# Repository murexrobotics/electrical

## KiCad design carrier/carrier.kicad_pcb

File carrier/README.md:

# Documentation

<https://docs.murexrobotics.com/elec/boards/carrier>

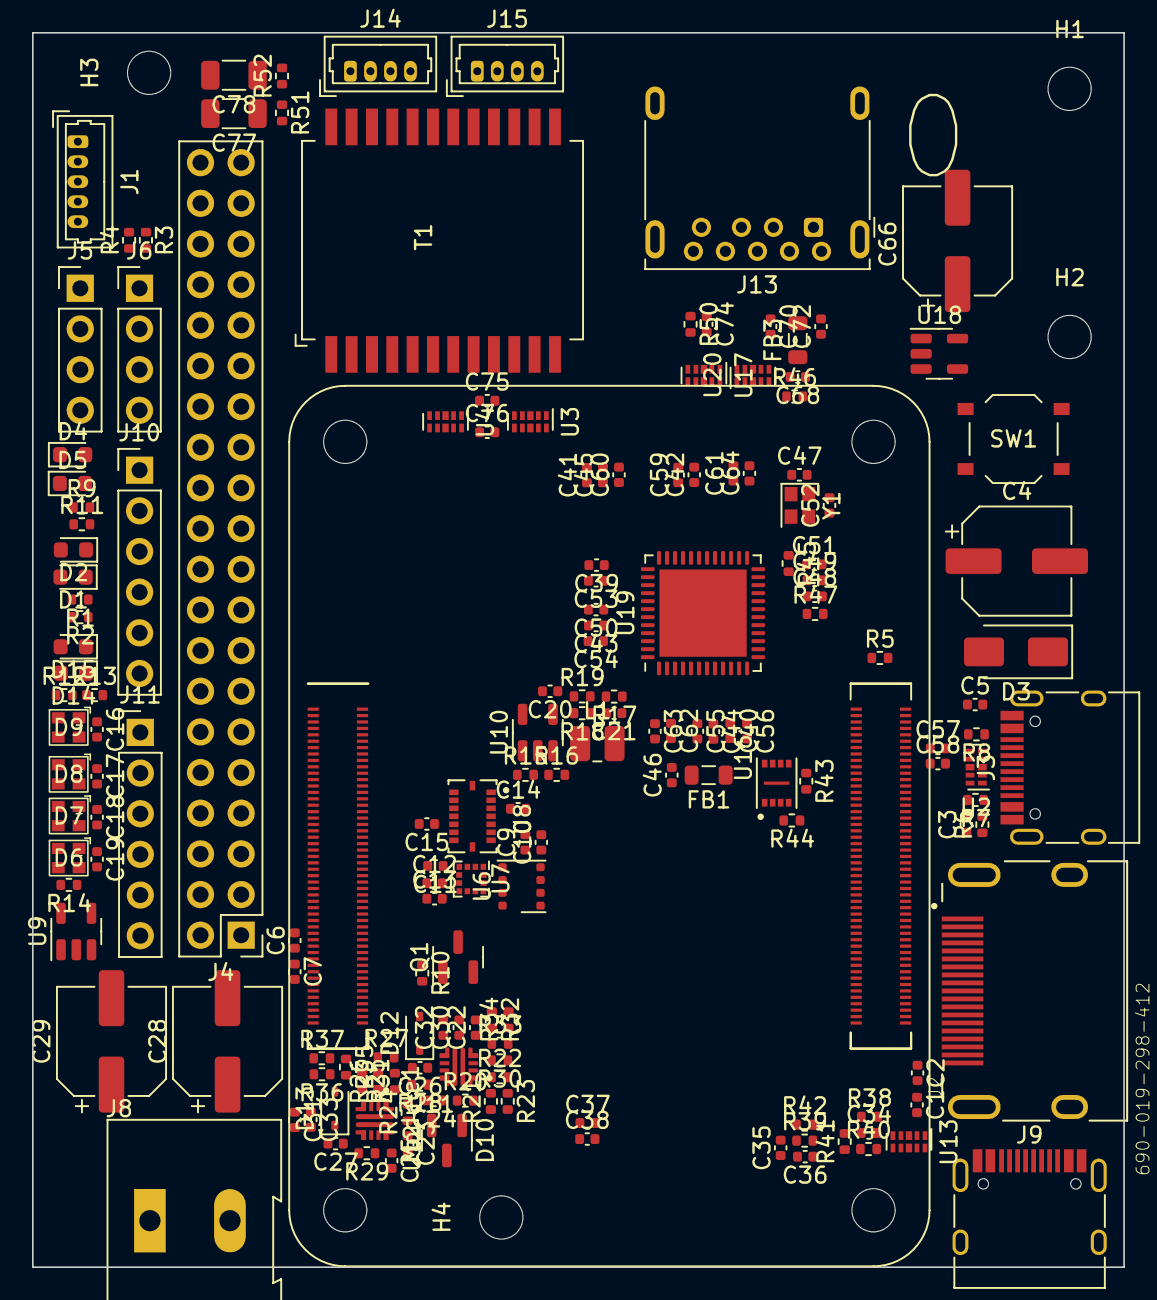
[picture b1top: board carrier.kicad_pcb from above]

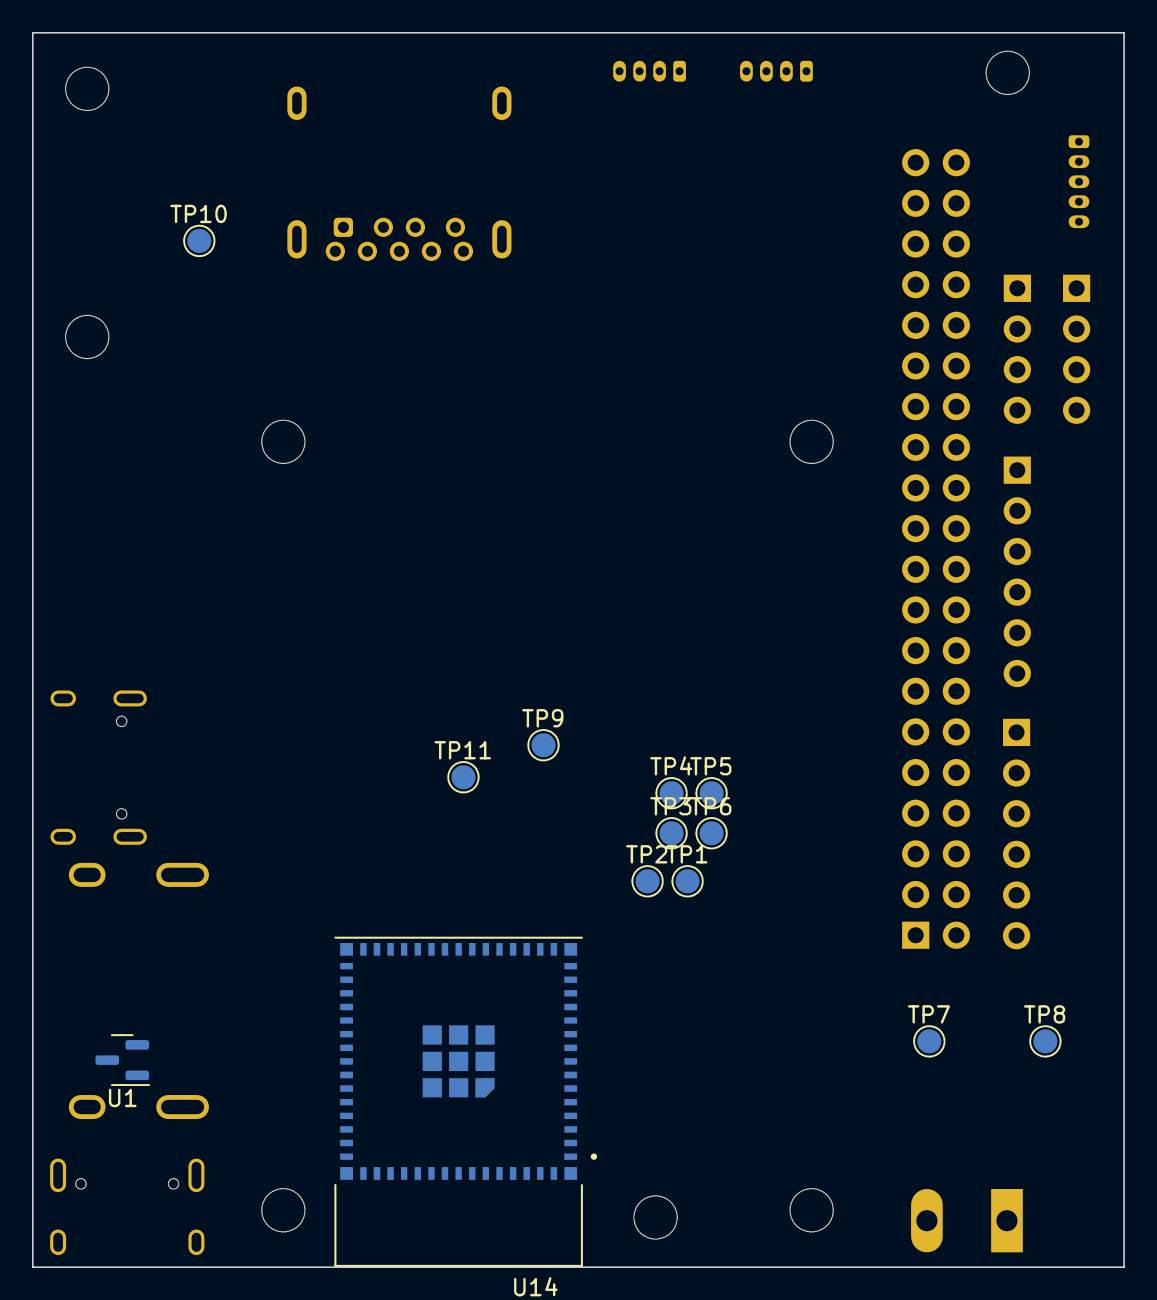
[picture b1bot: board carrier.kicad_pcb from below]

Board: 4 copper layers, 68.2 x 77.1 mm, 192 parts (13 on the bottom side), 178 nets, no tracks yet.

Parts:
C1, C2, C3, C5, C6, C9, C10, C11, C13, C14, C15, C34, C39, C40, C41, C42, C57, C58, C61, C62, C70, C72, C74: 100nF; C_0402_1005Metric
C4, C28, C29, C66: 150uF; CP_Elec_6.3x7.7
C7, C20, C30, C31, C32, C33, C46, C68: 10uF; C_0402_1005Metric
C12, C36: 1uF; C_0402_1005Metric
C16, C17, C18, C19, C35, C38, C75, C76: 0.1uF; C_0402_1005Metric
C21, C47, C52: 22pF; C_0402_1005Metric
C22, C23: 1uF X5R; C_0402_1005Metric
C24, C25: 2.2nF; C_0402_1005Metric
C26, C27: 3.3nF; C_0402_1005Metric
C37: 22uF; C_0402_1005Metric
C43, C44, C45, C48, C49, C50, C51, C53, C54, C55, C56, C59, C60, C63, C64: 10nF; C_0402_1005Metric
C77, C78: 1nF 2KV (1206); C_1206_3216Metric
D1: 5V; LED_0603_1608Metric
D2: 3.3V; LED_0603_1608Metric
D3: SS54; D_SMA
D4, D14: LED Green; LED_0603_1608Metric
D5: LED RED; LED_0603_1608Metric
D6, D7, D8, D9: NEOPIXEL; SK6812-EC20
D10: PSM712; SOT-23
D12, D13: 1N5819WS; D_SOD-323
D15: LED Orange; LED_0603_1608Metric
FB1, FB3: BLM21PG600SN1; L_0805_2012Metric
H1, H2, H3, H4: MountingHole; MountingHole_2.7mm_M2.5
H5: CM4 GPIO Hirose 2x50; Raspberry-Pi-4-Compute-Module-No-Outline-No-Pads
H6: CM4 High Speed Hirose 2x50; Raspberry-Pi-4-Compute-Module-No-Outline-No-Pads
J1: UART; Molex_PicoBlade_53047-0510_1x05_P1.25mm_Vertical
J2: 690-019-298-412; EDAC 690-019-298-412
J3, J9: USB_C_Receptacle_USB2.0; USB_C_Receptacle_HRO_TYPE-C-31-M-12
J4: THD-20-R; PinHeader_2x20_P2.54mm_Vertical
J5, J6: I2C; PinHeader_1x04_P2.54mm_Vertical
J8: External 5V Input; TerminalBlock_Altech_AK300-2_P5.00mm
J10: ESP GPIO 1; PinHeader_1x06_P2.54mm_Vertical
J11: ESP GPIO 2; PinHeader_1x06_P2.54mm_Vertical
J13: USB3_A; USB3_A_Molex_48393-001
J14, J15: Conn_01x04; Molex_PicoBlade_53047-0410_1x04_P1.25mm_Vertical
L1: 2.2uH; L_1008_2520Metric
Module1: ComputeModule4; Raspberry-Pi-4-Compute-Module
Q1: SS8550; SOT-23
R1, R2, R5, R10: 2.2k; R_0402_1005Metric
R3, R4, R23, R33, R42, R44, R47: 10k; R_0402_1005Metric
R6, R38, R50: 1M; R_0402_1005Metric
R7, R8: 56k; R_0402_1005Metric
R9, R11, R12, R13: 1k; R_0402_1005Metric
R14: 470; R_0402_1005Metric
R15, R16: 15k; R_0402_1005Metric
R17: 12k; R_0402_1005Metric
R18, R19: 8.2k; R_0402_1005Metric
R20, R24: 470k; R_0402_1005Metric
R21: 30k; R_0402_1005Metric
R22: 120k; R_0402_1005Metric
R25, R30, R31, R32, R35, R43: 47k; R_0402_1005Metric
R26: 220k; R_0402_1005Metric
R27: 33k; R_0402_1005Metric
R28: 760; R_0402_1005Metric
R29: 1.5k; R_0402_1005Metric
R34, R40, R41: 5.1k; R_0402_1005Metric
R36: 27k; R_0402_1005Metric
R37: 1.2k; R_0402_1005Metric
R39: 0; R_0402_1005Metric
R45: 680; R_0402_1005Metric
R46: 1.6k; R_0402_1005Metric
R51, R52: 75; R_0402_1005Metric
SW1: ESP RST; SW_Push_1P1T_XKB_TS-1187A
T1: QT24A23
TP1, TP2, TP3, TP4, TP5, TP6, TP7, TP8, TP9, TP10, TP11: TestPoint_Pad_D1.5mm
U1: RT9742SNGV; SOT-23
U2, U3, U4, U13, U17, U20: TPD4EUSB30; USON-10_2.5x1.0mm_P0.5mm
U6: BME680; Bosch_LGA-8_3x3mm_P0.8mm_ClockwisePinNumbering
U7: LIS3MDL; LGA-12_2x2mm_P0.5mm
U8: BMI088; PQFN50P450X300X100-16N
U9: SN74LV1T34DCK; SOT-23-5
U10: AP3429KTTR-G1; TSOT-23-5
U11, U12: TPS259474ARPWR; TPS259474
U14: ESP32-S3-MINI-1-N8; ESP32-S3-MINI-1
U16: W25X40CLUXIG
U18: AP2191; SOT-23-5
U19: uPD720202; QFN-48-1EP_7x7mm_P0.5mm_EP5.45x5.45mm
Y1: 24MHz; Crystal_SMD_2016-4Pin_2.0x1.6mm

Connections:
+3.3v: C9.1, C10.1, C14.1, C15.1, C29.1, C31.1, C33.1, C37.1, C38.1, C41.1, C43.1, C45.1, C49.1, C51.1, C54.1, C56.1, D4.2 (A), D13.1 (K), D14.2 (A), D15.2 (A), FB1.1, J4.1, J4.17, J5.3, J6.3, Q1.2 (E), R2.1, R3.1, R4.2, R15.1, R30.1, R31.1, R35.1, R42.1, R43.2, R44.1, R47.2, TP8.1, U6.2 (CSB), U6.5 (SDO), U6.6 (VDDIO), U6.8 (VDD), U7.10 (~CS), U8.3 (VDD), U8.11 (VDDIO), U12.6 (OUT), U14.3 (3V3), U16.7 (~HOLD), U16.8 (VCC), U19.12 (VDD33), U19.22 (VDD33), U19.34 (VDD33), U19.43 (VDD33)
/+1.05v: C21.1, C39.1, C40.1, C42.1, C44.1, C48.1, C50.1, C53.1, C55.1, C59.1, C60.1, L1.2, R17.1, TP9.1, U19.6 (VDD10), U19.9 (VDD10), U19.21 (VDD10), U19.30 (VDD10), U19.33 (VDD10), U19.39 (VDD10), U19.42 (VDD10)
/+5v: C1.1, C4.1, C5.1, C6.1, C7.1, C20.1, C28.1, C30.1, C32.1, D3.2 (A), D12.1 (K), J4.2, J4.4, Module1.77 (+5v_(Input)), Module1.79 (+5v_(Input)), Module1.81 (+5v_(Input)), Module1.83 (+5v_(Input)), Module1.85 (+5v_(Input)), Module1.87 (+5v_(Input)), R1.1, R7.2, R8.2, R32.1, TP7.1, U1.1 (IN), U10.4 (VIN), U11.6 (OUT), U18.5 (IN)
/CM4_GPIO/+3.3v_REF: Module1.78 (GPIO_VREF(1.8v/3.3v_Input)), Module1.84 (+3.3v_(Output)), Module1.86 (+3.3v_(Output))
/CM4_GPIO/BT_nDis: J4.27, Module1.89 (WiFi_nDisable), Module1.91 (BT_nDisable)
/CM4_GPIO/CT1: T1.7 (CT1), T1.10 (CT1)
/CM4_GPIO/CT2: C76.1, T1.1 (CT2), T1.4 (CT2)
/CM4_GPIO/ETH_LEDG: Module1.17 (Ethernet_nLED2(3.3v)), R12.2
/CM4_GPIO/ETH_LEDY: Module1.15 (Ethernet_nLED3(3.3v)), R13.2
/CM4_GPIO/GPIO6: J4.31, Module1.30 (GPIO6)
/CM4_GPIO/GPIO12: J4.32, Module1.31 (GPIO12)
/CM4_GPIO/GPIO13: J4.33, Module1.28 (GPIO13)
/CM4_GPIO/GPIO16: J4.36, Module1.29 (GPIO16)
/CM4_GPIO/GPIO17: J4.11, Module1.50 (GPIO17)
/CM4_GPIO/GPIO18: J4.12, Module1.49 (GPIO18), U9.2 (A)
/CM4_GPIO/GPIO19: J4.35, Module1.26 (GPIO19)
/CM4_GPIO/GPIO20: J4.38, Module1.27 (GPIO20)
/CM4_GPIO/GPIO21: J4.40, Module1.25 (GPIO21)
/CM4_GPIO/GPIO22: J4.15, Module1.46 (GPIO22)
/CM4_GPIO/GPIO23: J4.16, Module1.47 (GPIO23)
/CM4_GPIO/GPIO24: J4.18, Module1.45 (GPIO24)
/CM4_GPIO/GPIO25: J4.22, Module1.41 (GPIO25)
/CM4_GPIO/GPIO26: J4.37, Module1.24 (GPIO26)
/CM4_GPIO/GPIO27: J4.13, Module1.48 (GPIO27)
/CM4_GPIO/Neopixel/+5v: C16.2, C17.2, C18.2, C19.2, D6.1 (VDD), D7.1 (VDD), D8.1 (VDD), D9.1 (VDD), U9.5 (VCC)
/CM4_GPIO/REF1: C78.1, R52.2
/CM4_GPIO/REF2: C77.1, R51.2
/CM4_GPIO/TRD0+: J14.1, T1.23 (TX2+)
/CM4_GPIO/TRD0-: J14.2, T1.22 (TX2-)
/CM4_GPIO/TRD0_N: Module1.10 (Ethernet_Pair0_N), T1.3 (TD2-), U4.4 (D2+), U4.7
/CM4_GPIO/TRD0_P: Module1.12 (Ethernet_Pair0_P), T1.2 (TD2+), U4.5 (D2-), U4.6
/CM4_GPIO/TRD1+: J14.3, T1.20 (RX2+)
/CM4_GPIO/TRD1-: J14.4, T1.19 (RX2-)
/CM4_GPIO/TRD1_N: Module1.6 (Ethernet_Pair1_N), T1.6 (RD2-), U4.2 (D1-), U4.9
/CM4_GPIO/TRD1_P: Module1.4 (Ethernet_Pair1_P), T1.5 (RD2+), U4.1 (D1+), U4.10
/CM4_GPIO/TRD2+: J15.1, T1.17 (TX1+)
/CM4_GPIO/TRD2-: J15.2, T1.16 (TX1-)
/CM4_GPIO/TRD2_N: Module1.9 (Ethernet_Pair2_N), T1.9 (TD1-), U3.4 (D2+), U3.7
/CM4_GPIO/TRD2_P: Module1.11 (Ethernet_Pair2_P), T1.8 (TD1+), U3.5 (D2-), U3.6
/CM4_GPIO/TRD3+: J15.3, T1.14 (RX1+)
/CM4_GPIO/TRD3-: J15.4, T1.13 (RX1-)
/CM4_GPIO/TRD3_N: Module1.5 (Ethernet_Pair3_N), T1.12 (RD1-), U3.2 (D1-), U3.9
/CM4_GPIO/TRD3_P: Module1.3 (Ethernet_Pair3_P), T1.11 (RD1+), U3.1 (D1+), U3.10
/CM4_GPIO/nEXTRST: Module1.100 (nEXTRST), U19.11 (PONRSTB)
/CM4_GPIO/nPWR_LED: Module1.95 (nPI_LED_PWR), R10.1
/CM4_GPIO/nRPIBOOT: J4.28, Module1.93 (nRPIBOOT)
/CM4_HighSpeed/HDMI0_CEC: J2.13 (CEC), Module1.151 (HDMI0_CEC)
/CM4_HighSpeed/HDMI0_CK_N: J2.12 (CK-), Module1.190 (HDMI0_CLK_N)
/CM4_HighSpeed/HDMI0_CK_P: J2.10 (CK+), Module1.188 (HDMI0_CLK_P)
/CM4_HighSpeed/HDMI0_D0_N: J2.9 (D0-), Module1.184 (HDMI0_TX0_N)
/CM4_HighSpeed/HDMI0_D0_P: J2.7 (D0+), Module1.182 (HDMI0_TX0_P)
/CM4_HighSpeed/HDMI0_D1_N: J2.6 (D1-), Module1.178 (HDMI0_TX1_N)
/CM4_HighSpeed/HDMI0_D1_P: J2.4 (D1+), Module1.176 (HDMI0_TX1_P)
/CM4_HighSpeed/HDMI0_D2_N: J2.3 (D2-), Module1.172 (HDMI0_TX2_N)
/CM4_HighSpeed/HDMI0_D2_P: J2.1 (D2+), Module1.170 (HDMI0_TX2_P)
/CM4_HighSpeed/HDMI0_HOTPLUG: J2.19 (HPD/HEAC-), Module1.153 (HDMI0_HOTPLUG)
/CM4_HighSpeed/HDMI0_SCL: J2.15 (SCL), Module1.200 (HDMI0_SCL)
/CM4_HighSpeed/HDMI0_SDA: J2.16 (SDA), Module1.199 (HDMI0_SDA)
/CM4_HighSpeed/HDMI_5v: C2.1, J2.18 (+5V), U1.2 (OUT)
/CM4_HighSpeed/PCIE_CLK_N: Module1.112 (PCIe_CLK_N), U19.2 (PECLKN)
/CM4_HighSpeed/PCIE_CLK_P: Module1.110 (PCIe_CLK_P), U19.1 (PECLKP)
/CM4_HighSpeed/PCIE_CLK_nREQ: Module1.102 (PCIe_CLK_nREQ), U19.10 (PECREQB)
/CM4_HighSpeed/PCIE_RX_N: C58.1, Module1.118 (PCIe_RX_N)
/CM4_HighSpeed/PCIE_RX_P: C57.1, Module1.116 (PCIe_RX_P)
/CM4_HighSpeed/PCIE_TX_N: Module1.124 (PCIe_TX_N), U19.8 (PERXN)
/CM4_HighSpeed/PCIE_TX_P: Module1.122 (PCIe_TX_P), U19.7 (PERXP)
/CM4_HighSpeed/PCIE_nRST: Module1.109 (PCIe_nRST), U19.47 (PERSTB)
/CM4_HighSpeed/USB2_N: J3.A7 (D-), J3.B7 (D-), Module1.103 (USB2_N), U2.4 (D2+), U2.7
/CM4_HighSpeed/USB2_P: J3.A6 (D+), J3.B6 (D+), Module1.105 (USB2_P), U2.5 (D2-), U2.6
/CM4_HighSpeed/USB3/A+3.3v: C46.1, C61.1, C62.1, C63.1, C64.1, FB1.2, TP11.1, U19.3 (AVDD33), U19.25 (AVDD33)
/CM4_HighSpeed/USB3/OCI1B: R47.1, U18.3 (~FLG), U19.19 (OCI1B)
/CM4_HighSpeed/USB3/PPON1: U18.4 (EN), U19.20 (PPON1)
/CM4_HighSpeed/USB3/SPICSB: U16.1 (~CS), U19.14 (SPICSB)
/CM4_HighSpeed/USB3/SPISCK: U16.6 (SCK), U19.15 (SPISCK)
/CM4_HighSpeed/USB3/SPISI: U16.5 (DI(IO0)), U19.16 (SPISI)
/CM4_HighSpeed/USB3/SPISO: R43.1, U16.2 (DO(IO1)), U19.13 (SPISO)
/CM4_HighSpeed/USB3/U2DM1: J13.2 (D-), U17.2 (D1-), U17.9, U19.36 (U2DM1)
/CM4_HighSpeed/USB3/U2DP1: J13.3 (D+), U17.1 (D1+), U17.10, U19.35 (U2DP1)
/CM4_HighSpeed/USB3/U3RXDN1: J13.5 (SSRX-), U17.5 (D2-), U17.6, U19.32 (U3RXDN1)
/CM4_HighSpeed/USB3/U3RXDP1: J13.6 (SSRX+), U17.4 (D2+), U17.7, U19.31 (U3RXDP1)
/CM4_HighSpeed/USB3/U3TXDN1: C70.1, U19.29 (U3TXDN1), U20.5 (D2-), U20.6
/CM4_HighSpeed/USB3/U3TXDP1: C72.1, U19.28 (U3TXDP1), U20.4 (D2+), U20.7
/CM4_HighSpeed/USB3/VBUS1: C66.1, C68.1, FB3.1, TP10.1, U18.1 (OUT)
/CM4_HighSpeed/USBOTG_ID: Module1.101 (USB_OTG_ID), R5.1
/ESP32-S3/ADC1_CH0: J10.1, U14.5 (IO1)
/ESP32-S3/ADC1_CH1: J10.2, U14.6 (IO2)
/ESP32-S3/ADC1_CH2: J10.3, U14.7 (IO3)
/ESP32-S3/ADC1_CH3: J10.4, U14.8 (IO4)
/ESP32-S3/ADC1_CH4: R28.1, U11.9 (ILM), U14.9 (IO5)
/ESP32-S3/ADC2_CH0: J11.1, U14.15 (IO11)
/ESP32-S3/ADC2_CH1: J11.2, U14.16 (IO12)
/ESP32-S3/ADC2_CH2: J11.3, U14.17 (IO13)
/ESP32-S3/ADC2_CH3: J11.4, U14.18 (IO14)
/ESP32-S3/ADC2_CH4: R29.1, U12.9 (ILM), U14.19 (IO15)
/ESP32-S3/EN: C36.1, R39.2, R42.2, U14.45 (EN)
/ESP32-S3/TCK: J11.6, U14.38 (IO42)
/ESP32-S3/TDI: J10.6, U14.36 (IO40)
/ESP32-S3/TDO: J11.5, U14.37 (IO41)
/ESP32-S3/TMS: J10.5, U14.35 (IO39)
/ESP32-S3/USB_N: J9.A7 (D-), J9.B7 (D-), U13.5 (D2-), U13.6, U14.23 (IO19)
/ESP32-S3/USB_P: J9.A6 (D+), J9.B6 (D+), U13.4 (D2+), U13.7, U14.24 (IO20)
/Power/+3.3v_RAW: C23.1, D10.2 (A2), R24.1, U12.5 (IN)
/Power/+5v_RAW: C22.1, D10.1 (A1), J8.2, R20.1, U11.5 (IN)
/RPI_RX0: J1.1, J4.10, Module1.51 (GPIO15)
/RPI_RX1: J1.3, J4.29, Module1.34 (GPIO5)
/RPI_TX0: J1.2, J4.8, Module1.55 (GPIO14)
/RPI_TX1: J1.4, J4.7, Module1.54 (GPIO4)
/SCL: J4.5, J5.2, J6.2, Module1.56 (GPIO3), R3.2, U6.4 (SCK), U7.1 (SCL/SPC)
/SDA: J4.3, J5.1, J6.1, Module1.58 (GPIO2), R4.1, U6.3 (SDI), U7.11 (SDA/SDI/SDO)
/SPI0_CE0: J4.24, Module1.39 (GPIO8), U8.14 (CSB1)
/SPI0_CE1: J4.26, Module1.37 (GPIO7), U8.5 (CSB2)
/SPI0_CLK: J4.23, Module1.38 (GPIO11), U8.8 (SCL/SCK)
/SPI0_MISO: J4.21, Module1.40 (GPIO9), U8.10 (SDO2), U8.15 (SDO1)
/SPI0_MOSI: J4.19, Module1.44 (GPIO10), U8.9 (SDA/SDI)
/USB2/VBUS: D3.1 (K), J3.A4 (VBUS), J3.A9 (VBUS), J3.B4 (VBUS), J3.B9 (VBUS)
GND: C1.2, C2.2, C3.2, C4.2, C5.2, C6.2, C7.2, C9.2, C10.2, C11.2, C12.1, C13.1, C14.2, C15.2, C16.1, C17.1, C18.1, C19.1, C20.2, C22.2, C23.2, C24.2, C25.2, C26.2, C27.2, C28.2, C29.2, C30.2, C31.2, C32.2, C33.2, C34.2, C35.1, C36.2, C37.2, C38.2, C39.2, C40.2, C41.2, C42.2, C43.2, C44.2, C45.2, C46.2, C47.2, C48.2, C49.2, C50.2, C51.2, C52.2, C53.2, C54.2, C55.2, C56.2, C59.2, C60.2, C61.2, C62.2, C63.2, C64.2, C66.2, C68.2, C74.2, C75.2, C76.2, D1.1 (K), D2.1 (K), D6.3 (VSS), D7.3 (VSS), D8.3 (VSS), D9.3 (VSS), D10.3 (common), D12.2 (A), D13.2 (A), J1.5, J2.2 (D2S), J2.5 (D1S), J2.8 (D0S), J2.11 (CKS), J2.17 (GND), J2.SH1 (SH), J2.SH2 (SH), J2.SH3 (SH), J2.SH4 (SH), J3.A1 (GND), J3.A12 (GND), J3.B1 (GND), J3.B12 (GND), J4.6, J4.9, J4.14, J4.20, J4.25, J4.30, J4.34, J4.39, J5.4, J6.4, J8.1, J9.A1 (GND), J9.A12 (GND), J9.B1 (GND), J9.B12 (GND), J13.7 (DRAIN), J13.10 (SHIELD), Module1.1 (GND), Module1.2 (GND), Module1.7 (GND), Module1.8 (GND), Module1.13 (GND), Module1.14 (GND), Module1.22 (GND), Module1.23 (GND), Module1.32 (GND), Module1.33 (GND), Module1.42 (GND), Module1.43 (GND), Module1.52 (GND), Module1.53 (GND), Module1.59 (GND), Module1.60 (GND), Module1.65 (GND), Module1.66 (GND), Module1.71 (GND), Module1.74 (GND), Module1.98 (GND), Module1.107 (GND), Module1.108 (GND), Module1.113 (GND), Module1.114 (GND), Module1.119 (GND), Module1.120 (GND), Module1.125 (GND), Module1.126 (GND), Module1.131 (GND), Module1.132 (GND), Module1.137 (GND), Module1.138 (GND), Module1.144 (GND), Module1.150 (GND), Module1.155 (GND), Module1.156 (GND), Module1.161 (GND), Module1.162 (GND), Module1.167 (GND), Module1.168 (GND), Module1.173 (GND), Module1.174 (GND), Module1.179 (GND), Module1.180 (GND), Module1.185 (GND), Module1.186 (GND), Module1.191 (GND), Module1.192 (GND), Module1.197 (GND), Module1.198 (GND), R5.2, R6.2, R11.2, R16.2, R19.2, R23.2, R27.2, R28.2, R29.2, R34.2, R37.2, R38.2, R40.2, R41.2, R46.2, R50.2, SW1.1, U1.3 (GND), U2.3 (GND), U2.8 (GND), U3.3 (GND), U3.8 (GND), U4.3 (GND), U4.8 (GND), U6.1 (GND), U6.7 (GND), U7.2 (GND), U7.3 (GND), U7.9 (SDO/SA1), U7.12 (GND), U8.2 (NC), U8.4 (GNDA), U8.6 (GNDIO), U8.7 (PS), U9.3 (GND), U10.2 (GND), U11.8 (GND), U12.8 (GND), U13.3 (GND), U13.8 (GND), U14.1 (GND), U14.2 (GND), U14.42 (GND), U14.43 (GND), U14.46 (GND), U14.47 (GND), U14.48 (GND), U14.49 (GND), U14.50 (GND), U14.51 (GND), U14.52 (GND), U14.53 (GND), U14.54 (GND), U14.55 (GND), U14.56 (GND), U14.57 (GND), U14.58 (GND), U14.59 (GND), U14.60 (GND), U14.61 (GND), U14.61_1 (GND), U14.61_2 (GND), U14.61_3 (GND), U14.61_4 (GND), U14.61_5 (GND), U14.61_6 (GND), U14.61_7 (GND), U14.61_8 (GND), U14.62 (GND), U14.63 (GND), U14.64 (GND), U14.65 (GND), U16.4 (GND), U16.9 (GND), U17.3 (GND), U17.8 (GND), U18.2 (GND), U19.27 (IC(L)), U19.49 (GND_PAD), U20.3 (GND), U20.8 (GND), Y1.2, Y1.4
unnamed: C35.2, R39.1, SW1.2
unnamed: C52.1, R45.1, Y1.3
unnamed: D1.2 (A), R1.2
unnamed: D2.2 (A), R2.2
unnamed: D4.1 (K), R9.1
unnamed: D5.2 (A), Q1.3 (C)
unnamed: D5.1 (K), R11.1
unnamed: D6.4 (DIN), R14.2
unnamed: D6.2 (DOUT), D7.4 (DIN)
unnamed: D7.2 (DOUT), D8.4 (DIN)
unnamed: D8.2 (DOUT), D9.4 (DIN)
unnamed: D14.1 (K), R12.1
unnamed: D15.1 (K), R13.1
unnamed: J3.A5 (CC1), R7.1
unnamed: J3.B5 (CC2), R8.1
unnamed: C3.1, J3.S1 (SHIELD), R6.1
unnamed: J9.A5 (CC1), R40.1
unnamed: J9.B5 (CC2), R41.1
unnamed: C34.1, J9.S1 (SHIELD), R38.1
unnamed: C74.1, J13.4 (GND), R50.1
unnamed: C72.2, J13.9 (SSTX+)
unnamed: C70.2, J13.8 (SSTX-)
unnamed: FB3.2, J13.1 (VBUS)
unnamed: Module1.21 (PI_nLED_Activity), R9.2
unnamed: Q1.1 (B), R10.2
unnamed: R18.2, R19.1
unnamed: R22.2, R23.1
unnamed: R26.2, R27.1
unnamed: R33.2, R34.1
unnamed: R36.2, R37.1
unnamed: R51.1, T1.21 (CMG2), T1.24 (CMG2)
unnamed: R52.1, T1.15 (CMG1), T1.18 (CMG1)
unnamed: C11.1, U7.4 (C1)
unnamed: TP1.1, U7.8 (DRDY)
unnamed: TP2.1, U7.7 (INT)
unnamed: C12.2, C13.2, U7.5 (Vdd), U7.6 (Vdd_IO)
unnamed: TP3.1, U8.16 (INT1)
unnamed: TP4.1, U8.1 (INT2)
unnamed: TP5.1, U8.12 (INT3)
unnamed: TP6.1, U8.13 (INT4)
unnamed: R14.1, U9.4 (Y)
unnamed: R15.2, R16.1, U10.1 (EN)
unnamed: C21.2, R17.2, R18.1, U10.5 (FB)
unnamed: L1.1, U10.3 (LX)
unnamed: R20.2, R21.1, U11.1 (EN/UVLO)
unnamed: C24.1, U11.10 (ITIMER)
unnamed: R21.2, R22.1, U11.2 (OVLO)
unnamed: R30.2, U11.3 (PG)
unnamed: R32.2, R33.1, U11.4 (PGTH)
unnamed: C26.1, U11.7 (dVdt)
unnamed: R24.2, R25.1, U12.1 (EN/UVLO)
unnamed: C25.1, U12.10 (ITIMER)
unnamed: R25.2, R26.1, U12.2 (OVLO)
unnamed: R31.2, U12.3 (PG)
unnamed: R35.2, R36.1, U12.4 (PGTH)
unnamed: C27.1, U12.7 (dVdt)
unnamed: R44.2, U16.3 (~WP)
unnamed: C58.2, U19.5 (PETXN)
unnamed: C57.2, U19.4 (PETXP)
unnamed: R46.1, U19.26 (RREF)
unnamed: C47.1, U19.24 (XT1), Y1.1
unnamed: R45.2, U19.23 (XT2)

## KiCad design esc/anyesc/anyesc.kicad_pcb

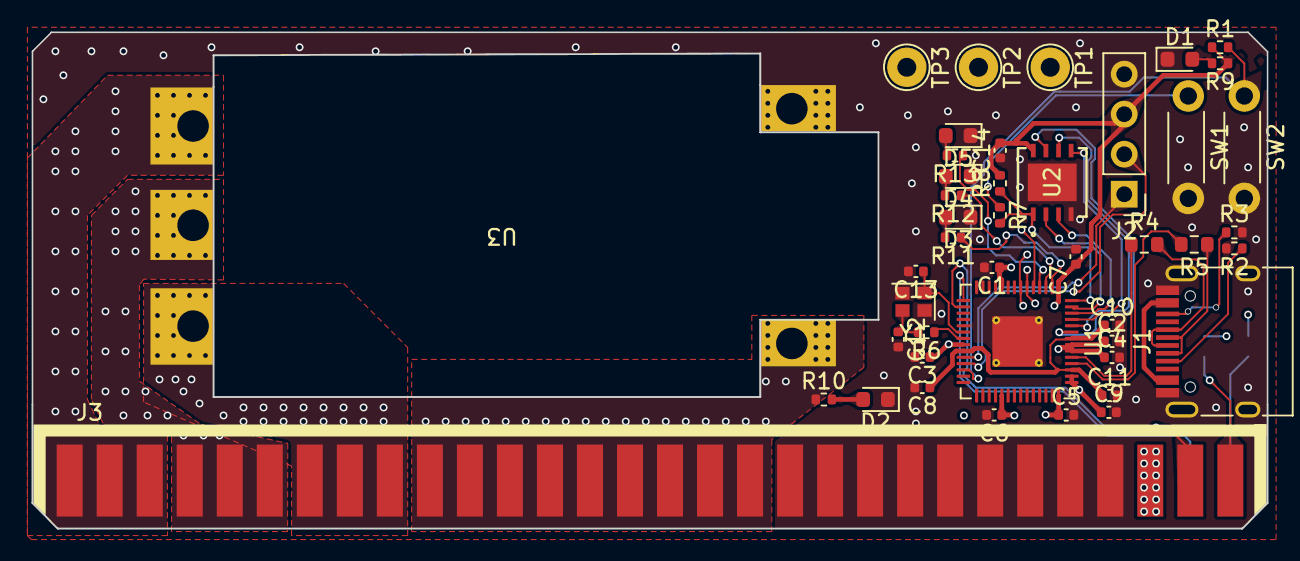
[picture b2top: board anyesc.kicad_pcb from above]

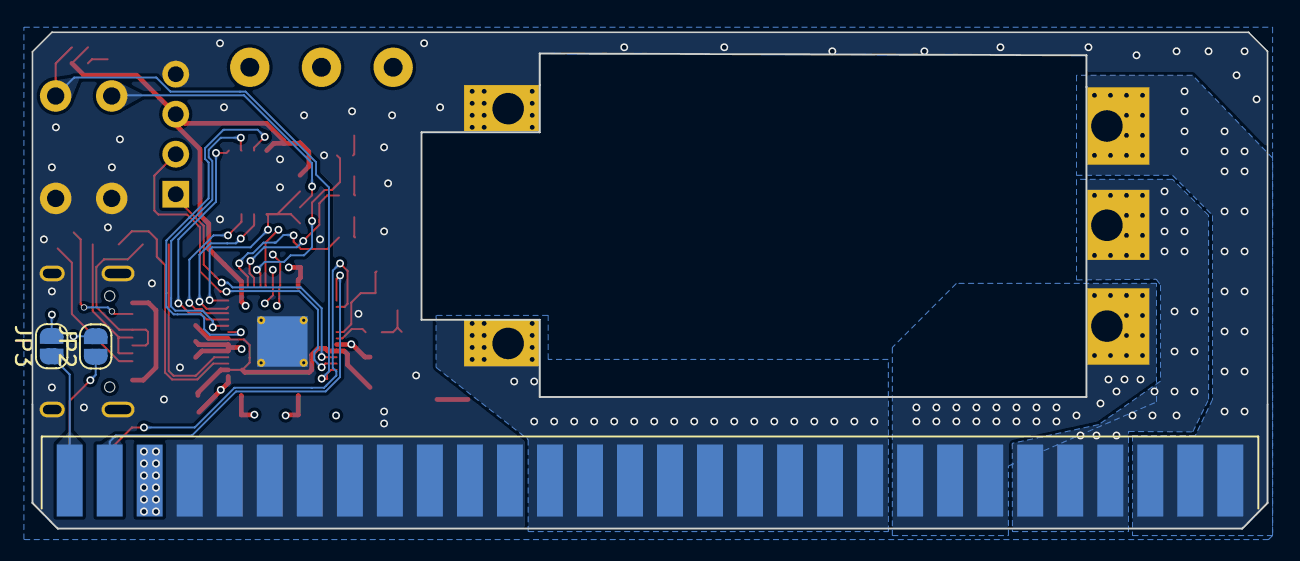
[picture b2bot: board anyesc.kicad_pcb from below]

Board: 4 copper layers, 78.4 x 31.5 mm, 46 parts (2 on the bottom side), 42 nets.

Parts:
C1, C2, C3, C4, C5, C6, C7, C8, C10: 0.1uF; C_0402_1005Metric
C9, C11, C14: 1uF; C_0402_1005Metric
C12, C13: 27pF; C_0402_1005Metric
D1, D2: LED; LED_0603_1608Metric
D3: LED0; LED_0603_1608Metric
D4: LED1; LED_0603_1608Metric
D5: LED2; LED_0603_1608Metric
J1: USB_C_Receptacle_USB2.0; USB_C_Receptacle_HRO_TYPE-C-31-M-12
J2: Conn_01x04; PinHeader_1x04_P2.54mm_Vertical
J3: 5530843-7; TE_5530843-7_PCB_Edge
JP2: RX; SolderJumper-2_P1.3mm_Open_RoundedPad1.0x1.5mm
JP3: TX; SolderJumper-2_P1.3mm_Open_RoundedPad1.0x1.5mm
R1, R8: 10K; R_0402_1005Metric
R2, R3: 5.1k; R_0402_1005Metric
R4, R5: 27; R_0603_1608Metric
R6, R7: 1K; R_0402_1005Metric
R9, R10, R11, R12, R13: 1k; R_0402_1005Metric
SW1, SW2: SW_Push; SW_PUSH_6mm_SLIM
TP1: ESC_TX; TestPoint_THTPad_D2.5mm_Drill1.2mm
TP2: ESC_RX; TestPoint_THTPad_D2.5mm_Drill1.2mm
TP3: ESC_PWM; TestPoint_THTPad_D2.5mm_Drill1.2mm
U1: RP2040; QFN-56-1EP_7x7mm_P0.4mm_EP3.2x3.2mm_ThermalVias
U2: W25Q64JVXGIQ; DFN_XGIQ TR_WIN-M
U3: B-G431B-ESC1; B-G431B-ESC1_MOUNT
Y1: 12MHz; Crystal_SMD_2016-4Pin_2.0x1.6mm

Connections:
+3V3: C1.1, C2.1, C3.1, C4.1, C5.1, C6.1, C7.1, C9.1, C14.2, J2.3, J3.55, J3.56, R1.1, R8.2, R9.1, U1.1 (IOVDD), U1.10 (IOVDD), U1.22 (IOVDD), U1.33 (IOVDD), U1.42 (IOVDD), U1.43 (ADC_AVDD), U1.44 (VREG_VIN), U1.48 (USB_VDD), U1.49 (IOVDD), U2.8 (VCC)
+12V: J3.19, J3.20, J3.21, J3.22, J3.23, J3.24, J3.25, J3.26, J3.27, J3.28, J3.29, J3.30, J3.31, J3.32, J3.33, J3.34, J3.35, J3.36, R10.1, U3.1 (V+)
/BOARD_RX: J3.58, U1.16 (GPIO13)
/BOARD_RX_1: J3.60, JP2.1 (A)
/BOARD_TX: J3.57, U1.15 (GPIO12)
/BOARD_TX_1: J3.59, JP3.1 (A)
/ESC_PWM: TP3.1, U1.5 (GPIO3)
/PHASE_A: J3.1, J3.2, J3.3, J3.4, J3.5, J3.6, U3.3 (A)
/PHASE_B: J3.7, J3.8, J3.9, J3.10, J3.11, J3.12, U3.4 (B)
/PHASE_C: J3.13, J3.14, J3.15, J3.16, J3.17, J3.18, U3.5 (C)
/RP2040/+1.1V: C8.1, C10.1, C11.1, U1.23 (DVDD), U1.45 (VREG_VOUT), U1.50 (DVDD)
/RP2040/LED0: R11.1, U1.2 (GPIO0)
/RP2040/LED1: R12.1, U1.3 (GPIO1)
/RP2040/LED2: R13.1, U1.4 (GPIO2)
/RP2040/QSPI_CS: R7.2, R8.1, U1.56 (QSPI_SS_N), U2.1 (~CS)
/RP2040/QSPI_SCK: U1.52 (QSPI_SCLK), U2.6 (CLK)
/RP2040/QSPI_SD0: U1.53 (QSPI_SD0), U2.5 (DI(IO0))
/RP2040/QSPI_SD1: U1.55 (QSPI_SD1), U2.2 (DO(IO1))
/RP2040/QSPI_SD2: U1.54 (QSPI_SD2), U2.3 (IO2)
/RP2040/QSPI_SD3: U1.51 (QSPI_SD3), U2.7 (IO3)
/RP2040/RUN: R1.2, SW2.1, U1.26 (RUN)
/RP2040/SWCLK: J2.1, U1.24 (SWCLK)
/RP2040/SWDIO: J2.2, U1.25 (SWDIO)
/RP2040/USB_BOOT: R7.1, SW1.1
/RP2040/USB_N: J1.A7 (D-), J1.B7 (D-), R5.1
/RP2040/USB_P: J1.A6 (D+), J1.B6 (D+), R4.2
/RP2040/USB_VBUS: J1.A4 (VBUS), J1.A9 (VBUS), J1.B4 (VBUS), J1.B9 (VBUS)
/RP2040/XIN: C13.1, U1.20 (XIN), Y1.1
/RP2040/XOUT: R6.1, U1.21 (XOUT)
/UART1_RX: JP2.2 (B), TP2.1, U1.7 (GPIO5)
/UART1_TX: JP3.2 (B), TP1.1, U1.6 (GPIO4)
GND: C1.2, C2.2, C3.2, C4.2, C5.2, C6.2, C7.2, C8.2, C9.2, C10.2, C11.2, C12.2, C13.2, C14.1, D1.1 (K), D2.1 (K), D3.1 (K), D4.1 (K), D5.1 (K), J1.A1 (GND), J1.A12 (GND), J1.B1 (GND), J1.B12 (GND), J1.S1 (SHIELD), J2.4, J3.37, J3.38, J3.39, J3.40, J3.41, J3.42, J3.43, J3.44, J3.45, J3.46, J3.47, J3.48, J3.49, J3.50, J3.51, J3.52, J3.53, J3.54, R2.2, R3.2, SW1.2, SW2.2, U1.19 (TESTEN), U1.57 (GND), U2.4 (GND), U3.2 (V+), Y1.2, Y1.4
unnamed: C12.1, R6.2, Y1.3
unnamed: D1.2 (A), R9.2
unnamed: D2.2 (A), R10.2
unnamed: D3.2 (A), R11.2
unnamed: D4.2 (A), R12.2
unnamed: D5.2 (A), R13.2
unnamed: J1.A5 (CC1), R2.1
unnamed: J1.B5 (CC2), R3.1
unnamed: R5.2, U1.46 (USB_DM)
unnamed: R4.1, U1.47 (USB_DP)

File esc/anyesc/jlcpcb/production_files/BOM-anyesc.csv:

Comment,Designator,Footprint,LCSC
1k,"R10,R11,R12,R13,R6,R7,R9",R_0402_1005Metric,C11702
0.1uF,"C1,C10,C2,C3,C4,C5,C6,C7,C8",C_0402_1005Metric,C1525
30pF,"C12,C13",C_0603_1608Metric,C1658
USB_C_Receptacle_USB2.0,J1,USB_C_Receptacle_HRO_TYPE-C-31-M-12,C165948
RP2040,U1,QFN-56-1EP_7x7mm_P0.4mm_EP3.2x3.2mm_ThermalVias,C2040
LED0,D3,LED_0603_1608Metric,C2286
LED,D1,LED_0603_1608Metric,C2290
27,"R4,R5",R_0603_1608Metric,C25190
10K,"R1,R8",R_0402_1005Metric,C25744
5.1k,"R2,R3",R_0402_1005Metric,C25905
W25Q64JVXGIQ,U2,DFN_XGIQ TR_WIN-M,C2940195
1uF,"C11,C14,C9",C_0402_1005Metric,C52923
LED,D2,LED_0603_1608Metric,C72038
LED1,D4,LED_0603_1608Metric,C72041
LED2,D5,LED_0603_1608Metric,C72043
12MHz,Y1,Crystal_SMD_3225-4Pin_3.2x2.5mm,C9002
SW_Push,SW2,SW_PUSH_6mm_SLIM,
ESC Mount,H5,Adjustable_ESC_Mount,
ESC Mount,H4,Adjustable_ESC_Mount,
Conn_01x04,J2,PinHeader_1x04_P2.54mm_Vertical,
B-G431B-ESC1,U3,B-G431B-ESC1_MOUNT,
ESC_PWM,TP3,TestPoint_THTPad_D2.5mm_Drill1.2mm,
ESC_RX,TP2,TestPoint_THTPad_D2.5mm_Drill1.2mm,
5530843-7,J3,TE_5530843-7_PCB_Edge,
ESC Mount,H6,Adjustable_ESC_Mount,
SW_Push,SW1,SW_PUSH_6mm_SLIM,
ESC_TX,TP1,TestPoint_THTPad_D2.5mm_Drill1.2mm,
RX,JP2,SolderJumper-2_P1.3mm_Open_RoundedPad1.0x1.5mm,
TX,JP3,SolderJumper-2_P1.3mm_Open_RoundedPad1.0x1.5mm,

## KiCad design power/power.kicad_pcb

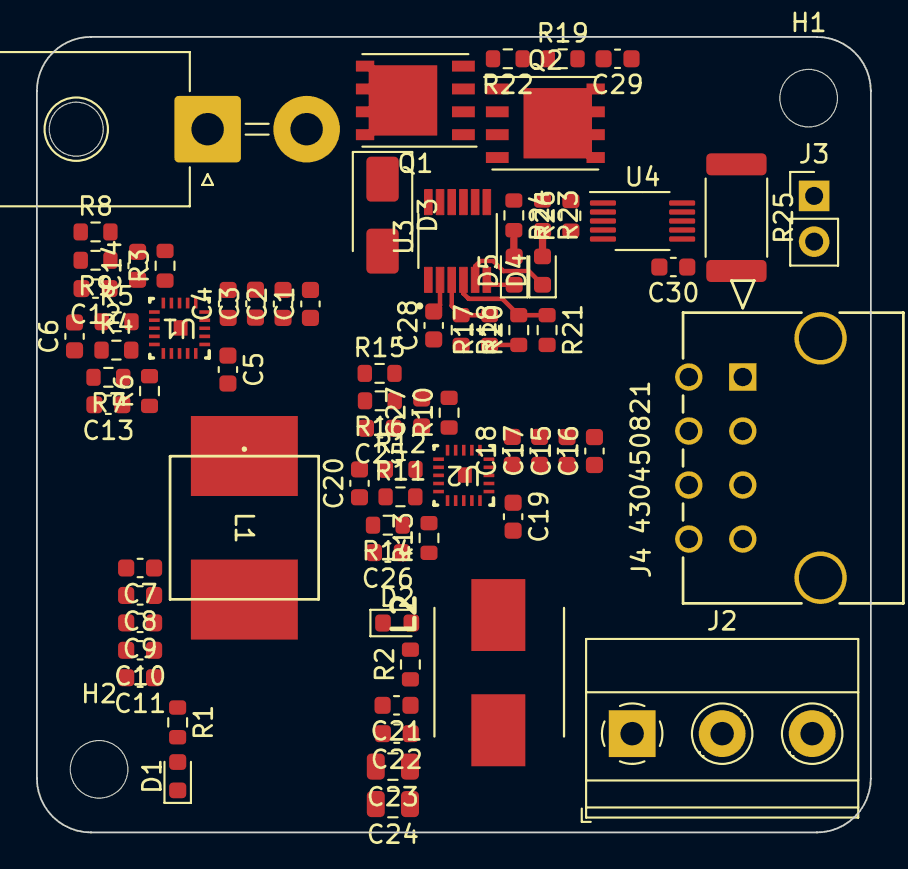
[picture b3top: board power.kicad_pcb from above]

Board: 4 copper layers, 46.3 x 44.2 mm, 76 parts (1 on the bottom side), 39 nets.

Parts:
C1, C2, C8, C9, C10, C11, C15, C16, C22: 22uF; C_0603_1608Metric
C3, C7, C17, C21: 1uF; C_0603_1608Metric
C4, C5, C12, C13, C18, C19, C25, C26, C28, C29, C30: 0.1uF; C_0603_1608Metric
C6: 47pF; C_0603_1608Metric
C14, C27: 22nF; C_0603_1608Metric
C20: 56pF; C_0603_1608Metric
C23, C24: 100uF; C_0805_2012Metric
D1, D2, D4, D5: LED; LED_0603_1608Metric
D3: SMAJ14A; D_SMA
H1, H2: MountingHole; MountingHole_3.2mm_M3
J1: Conn_01x02; Molex_Mega-Fit_76825-0002_2x01_P5.70mm_Horizontal
J2: Screw_Terminal_01x03; TerminalBlock_Phoenix_MKDS-1,5-3_1x03_P5.00mm_Horizontal
J3: Conn_01x02_Pin; PinHeader_1x02_P2.54mm_Vertical
J4: Conn_01x08; CON_430450821_MOL
JP1: TO_VS; SolderJumper-2_P1.3mm_Open_RoundedPad1.0x1.5mm
L1: 1.8uH; IND_XAL7070_COC-L
L2: 1.5uH; WE-HCI_7030_7040_705023
Q1, Q2: SIRA00DP; PowerPAK_SO-8_Single
R1, R2: 1k; R_0603_1608Metric
R3, R10, R20: 100k; R_0603_1608Metric
R4: 226k; R_0603_1608Metric
R5: 30k; R_0603_1608Metric
R6, R7: 51k; R_0603_1608Metric
R8: 26.6k; R_0603_1608Metric
R9, R14, R16: 5.1k; R_0603_1608Metric
R11: 91k; R_0603_1608Metric
R12: 20k; R_0603_1608Metric
R13: 330k; R_0603_1608Metric
R15: 8.87k; R_0603_1608Metric
R17: 105k; R_0603_1608Metric
R18: 5.11k; R_0603_1608Metric
R19, R26: 10k; R_0603_1608Metric
R21: 3k; R_0603_1608Metric
R22: 10; R_0603_1608Metric
R23, R24: 2.7k; R_0603_1608Metric
R25: 3mΩ; R_2512_6332Metric
U1, U2: TPS568230RJER; RJE0020A
U3: LTC4352CMS; SOP65P490X110-12N
U4: INA226; VSSOP-10_3x3mm_P0.5mm

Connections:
/3.3V: C30.1, R26.1, U4.2 (A0), U4.6 (VS)
/+3.3V: C20.1, C21.1, C22.1, C23.1, C24.1, J2.2, J4.6, L2.2, R2.1, R11.1
/Ideal Diode Controller/FAULT: D5.1 (K), U3.6 (FAULT)
/Ideal Diode Controller/GATE: Q2.4 (G), R19.1, R22.1, U3.11 (GATE)
/Ideal Diode Controller/OV: R20.2, R21.1, U3.4 (OV)
/Ideal Diode Controller/SOURCE: Q1.1 (S), Q1.2 (S), Q1.3 (S), Q2.1 (S), Q2.2 (S), Q2.3 (S), U3.12 (SOURCE)
/Ideal Diode Controller/STATUS: D4.1 (K), U3.5 (STATUS)
/Ideal Diode Controller/UV: R17.2, R18.1, U3.3 (UV)
/Ideal Diode Controller/VIN: D3.1 (A1), J1.2, Q1.5 (D), R17.1, R20.1, U3.1 (VIN)
/SCL: J3.1, U4.5 (SCL)
/SDA: J3.2, U4.4 (SDA)
/Stage 1 Step Down/BST: C5.1, U1.1 (BST)
/Stage 1 Step Down/EN: C12.1, R8.2, R9.1, U1.12 (EN)
/Stage 1 Step Down/FB: C6.2, R4.2, R5.1, U1.14 (FB)
/Stage 1 Step Down/MODE: R6.2, R7.1, U1.15 (MODE)
/Stage 1 Step Down/PGOOD: R3.1, U1.9 (PGOOD)
/Stage 1 Step Down/SS: C14.1, U1.11 (SS)
/Stage 1 Step Down/SW: C5.2, L1.1, U1.6 (SW), U1.19 (SW), U1.20 (SW)
/Stage 1 Step Down/VCC: C13.1, R3.2, R6.1, U1.17 (VCC)
/Stage 2 Step Down/BST: C19.1, U2.1 (BST)
/Stage 2 Step Down/EN: C25.1, R15.2, R16.1, U2.12 (EN)
/Stage 2 Step Down/FB: C20.2, R11.2, R12.1, U2.14 (FB)
/Stage 2 Step Down/MODE: R13.2, R14.1, U2.15 (MODE)
/Stage 2 Step Down/PGOOD: R10.1, U2.9 (PGOOD)
/Stage 2 Step Down/SS: C27.1, U2.11 (SS)
/Stage 2 Step Down/SW: C19.2, L2.1, U2.6 (SW), U2.19 (SW), U2.20 (SW)
/Stage 2 Step Down/VCC: C26.1, R10.2, R13.1, U2.17 (VCC)
/Stage 2 Step Down/VIN: C6.1, C7.1, C8.1, C9.1, C10.1, C11.1, C15.1, C16.1, C17.1, C18.1, J2.1, L1.2, R1.1, R4.1, R15.1, U2.2 (VIN), U2.3 (VIN), U2.4 (VIN), U2.5 (VIN)
/VIN+: Q2.5 (D), R23.1, R24.1, R25.1, U3.8 (OUT), U4.10 (Vin+)
/VIN-: C1.1, C2.1, C3.1, C4.1, J4.1, J4.2, J4.5, R8.1, R25.2, U1.2 (VIN), U1.3 (VIN), U1.4 (VIN), U1.5 (VIN), U4.8 (Vbus), U4.9 (Vin-)
GND: C1.2, C2.2, C3.2, C4.2, C7.2, C8.2, C9.2, C10.2, C11.2, C12.2, C13.2, C14.2, C15.2, C16.2, C17.2, C18.2, C21.2, C22.2, C23.2, C24.2, C25.2, C26.2, C27.2, C28.1, C29.1, C30.2, D1.1 (K), D2.1 (K), D3.2 (A2), J1.1, J2.3, J4.3, J4.4, J4.7, J4.8, JP1.2 (B), R5.2, R7.2, R9.2, R12.2, R14.2, R16.2, R18.2, R21.2, U1.7 (PGND), U1.8 (PGND), U1.10 (NC), U1.13 (AGND), U1.16 (NC), U1.18 (PGND), U1.21 (PGND), U2.7 (PGND), U2.8 (PGND), U2.10 (NC), U2.13 (AGND), U2.16 (NC), U2.18 (PGND), U2.21 (PGND), U3.7 (REV), U3.9 (GND), U4.7 (GND)
unnamed: C29.2, R19.2
unnamed: D1.2 (A), R1.2
unnamed: D2.2 (A), R2.2
unnamed: D4.2 (A), R23.2
unnamed: D5.2 (A), R24.2
unnamed: JP1.1 (A), R26.2, U4.1 (A1)
unnamed: Q1.4 (G), R22.2
unnamed: C28.2, U3.2 (VCC)
